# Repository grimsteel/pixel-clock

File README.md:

# The Pixel Clock

A clock-shaped PCB with 8 Neopixels and a buzzer. Built on a `CH552` MCU. Powered by two rechargeable LIR2032s.

Although this cannot actually be used as a clock, it can be used to play songs, with the neopixels flashing in sync.

Firmware using [ch554_sdcc](https://github.com/Blinkinlabs/ch554_sdcc) is in the firmware directory.

[gerber.zip](https://gerber.zip/2d/?boardUrl=%20https%3A%2F%2Fraw.githubusercontent.com%2Fgrimsteel%2Fpixel-clock%2Frefs%2Fheads%2Fmain%2Fproduction%2Fhacky-holidays.zip)

---

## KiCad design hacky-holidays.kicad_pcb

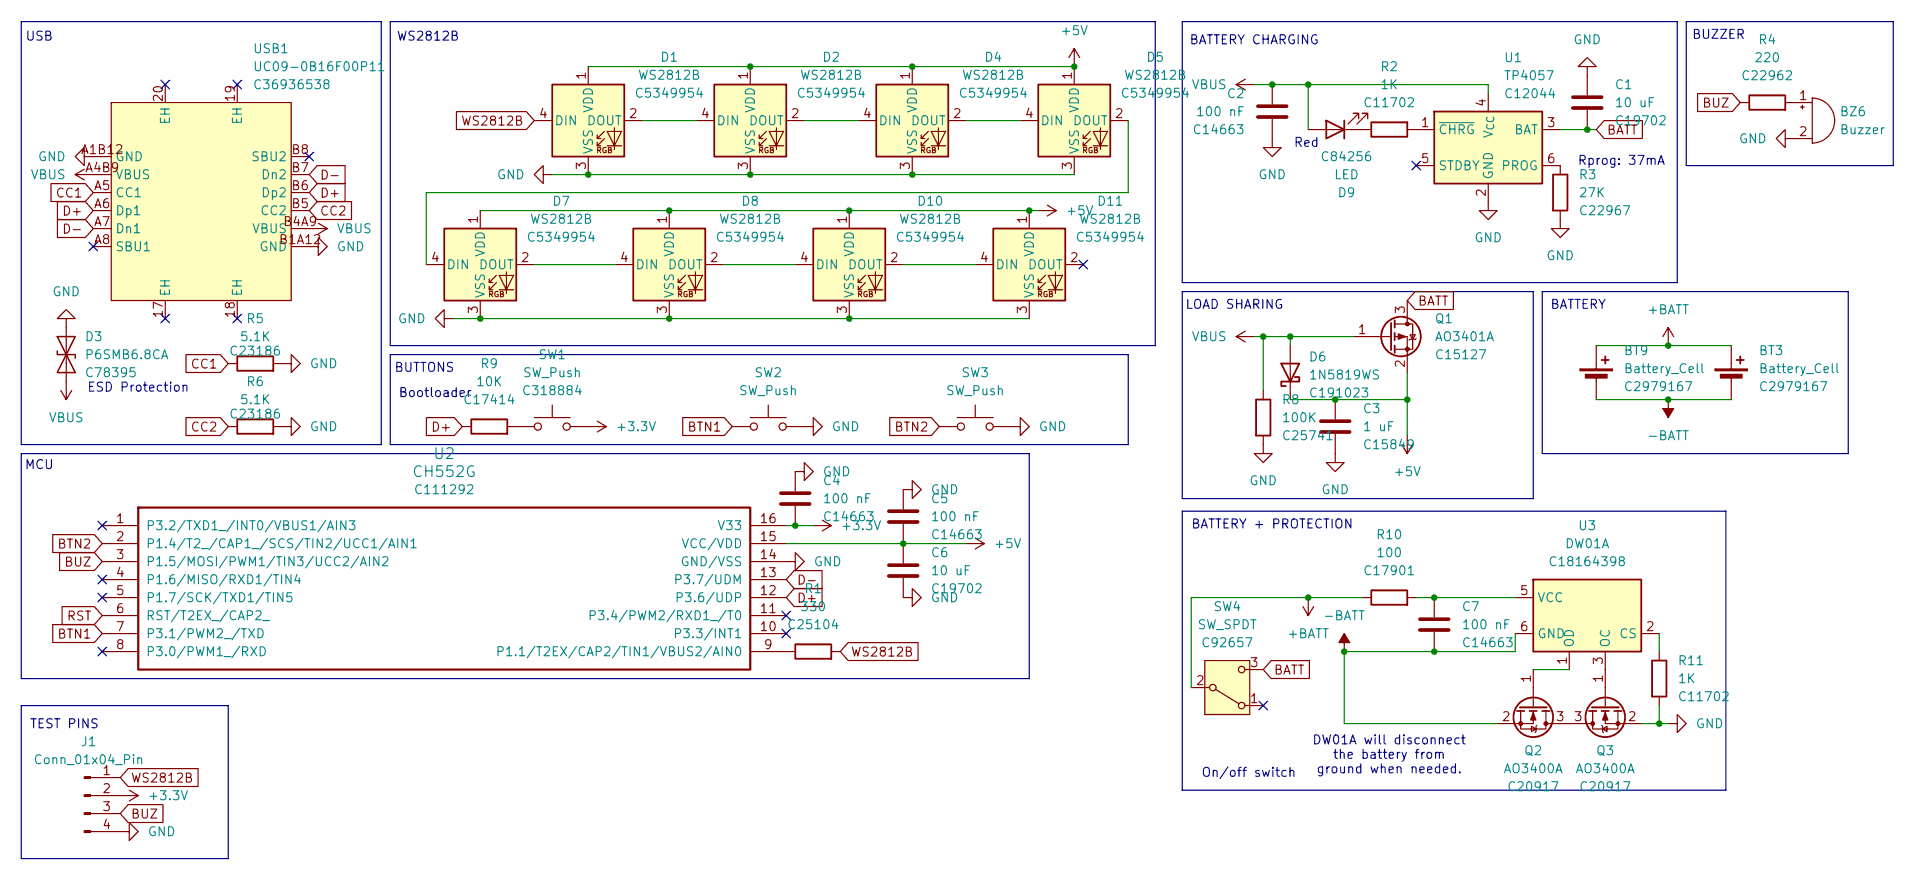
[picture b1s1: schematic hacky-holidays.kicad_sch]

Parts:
BT3, BT9: Battery_Cell; BatteryHolder_MYOUNG_BS-07-A1BJ001_CR2032; LCSC C2979167
BZ6: Buzzer; Buzzer_12x9.5RM7.6
C1, C6: 10 uF; C_0603_1608Metric; LCSC C19702
C2, C4, C5, C7: 100 nF; C_0603_1608Metric; LCSC C14663
C3: 1 uF; C_0603_1608Metric; LCSC C15849
D1, D2, D4, D5, D7, D8, D10, D11: WS2812B; LED-SMD_4P-L1.6-W1.5_XL-1615RGBC-WS2812B; LCSC C5349954
D3: P6SMB6.8CA; D_SMB; LCSC C78395
D6: 1N5819WS; D_SOD-323; LCSC C191023
D9: LED; LED_0805_2012Metric; LCSC C84256
J1: Conn_01x04_Pin; PinHeader_1x04_P2.54mm_Vertical
Q1: AO3401A; SOT-23; LCSC C15127
Q2, Q3: AO3400A; SOT-23; LCSC C20917
R1: 330; R_0402_1005Metric; LCSC C25104
R2, R11: 1K; R_0402_1005Metric; LCSC C11702
R3: 27K; R_0603_1608Metric; LCSC C22967
R4: 220; R_0603_1608Metric; LCSC C22962
R5, R6: 5.1K; R_0603_1608Metric; LCSC C23186
R8: 100K; R_0402_1005Metric; LCSC C25741
R9: 10K; R_0805_2012Metric; LCSC C17414
R10: 100; R_1206_3216Metric; LCSC C17901
SW1: SW_Push; SW_Push_1P1T_XKB_TS-1187A; LCSC C318884
SW2, SW3: SW_Push; SW_PUSH-12mm
SW4: SW_SPDT; SW-TH_K3-1260D-L1; LCSC C92657
U1: TP4057; SOT-23-6; LCSC C12044
U2: CH552G; STC_SOP-16_3.9x9.9mm_P1.27mm; LCSC C111292
U3: DW01A; SOT-23-6; LCSC C18164398
USB1: UC09-0B16F00P11; USB-C_UC09-0B16F00P11; LCSC Part C36936538

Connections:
+3.3V: C4.2, J1.2, SW1.2, U2.16 (V33)
+5V: C3.1, C5.1, C6.2, D1.1 (VDD), D2.1 (VDD), D4.1 (VDD), D5.1 (VDD), D6.1 (K), D7.1 (VDD), D8.1 (VDD), D10.1 (VDD), D11.1 (VDD), Q1.2 (S), U2.15 (VCC/VDD)
+BATT: BT3.1 (+), BT9.1 (+), R10.1, SW4.2 (B)
-BATT: BT3.2 (-), BT9.2 (-), C7.2, Q2.2 (S), U3.6 (GND)
BATT: C1.2, Q1.3 (D), SW4.3 (C), U1.3 (BAT)
BTN1: SW2.1, U2.7 (P3.1/PWM2_/TXD)
BTN2: SW3.1, U2.2 (P1.4/T2_/CAP1_/SCS/TIN2/UCC1/AIN1)
BUZ: J1.3, R4.1, U2.3 (P1.5/MOSI/PWM1/TIN3/UCC2/AIN2)
CC1: R5.1, USB1.A5 (CC1)
CC2: R6.1, USB1.B5 (CC2)
D+: R9.1, U2.12 (P3.6/UDP), USB1.A6 (Dp1), USB1.B6 (Dp2)
D-: U2.13 (P3.7/UDM), USB1.A7 (Dn1), USB1.B7 (Dn2)
GND: BZ6.2 (-), C1.1, C2.2, C3.2, C4.1, C5.2, C6.1, D1.3 (VSS), D2.3 (VSS), D3.2 (A2), D4.3 (VSS), D5.3 (VSS), D7.3 (VSS), D8.3 (VSS), D10.3 (VSS), D11.3 (VSS), J1.4, Q3.2 (S), R3.2, R5.2, R6.2, R8.2, R11.2, SW2.2, SW3.2, U1.2 (GND), U2.14 (GND/VSS), USB1.A1B12 (GND), USB1.B1A12 (GND)
unnamed: BZ6.1 (+), R4.2
unnamed: D1.2 (DOUT), D2.4 (DIN)
unnamed: D2.2 (DOUT), D4.4 (DIN)
unnamed: D4.2 (DOUT), D5.4 (DIN)
unnamed: D5.2 (DOUT), D7.4 (DIN)
unnamed: D7.2 (DOUT), D8.4 (DIN)
unnamed: D9.1 (K), R2.1
unnamed: D8.2 (DOUT), D10.4 (DIN)
unnamed: D10.2 (DOUT), D11.4 (DIN)
unnamed: Q2.3 (D), Q3.3 (D)
unnamed: Q2.1 (G), U3.1 (OD)
unnamed: Q3.1 (G), U3.3 (OC)
unnamed: R9.2, SW1.1
unnamed: R3.1, U1.6 (PROG)
unnamed: R2.2, U1.1 (~CHRG)
unnamed: R1.1, U2.9 (P1.1/T2EX/CAP2/TIN1/VBUS2/AIN0)
unnamed: R11.1, U3.2 (CS)
unnamed: C7.1, R10.2, U3.5 (VCC)
RST: U2.6 (RST/T2EX_/CAP2_)
VBUS: C2.1, D3.1 (A1), D6.2 (A), D9.2 (A), Q1.1 (G), R8.1, U1.4 (V_{CC}), USB1.A4B9 (VBUS), USB1.B4A9 (VBUS)
WS2812B: D1.4 (DIN), J1.1, R1.2

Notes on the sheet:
Bootloader
On/off switch
MCU
BATTERY
DW01A will disconnect the battery from ground when needed.
Rprog: 37mA
BUZZER
Red
USB
BUTTONS
BATTERY CHARGING
BATTERY + PROTECTION
TEST PINS
LOAD SHARING
WS2812B
ESD Protection

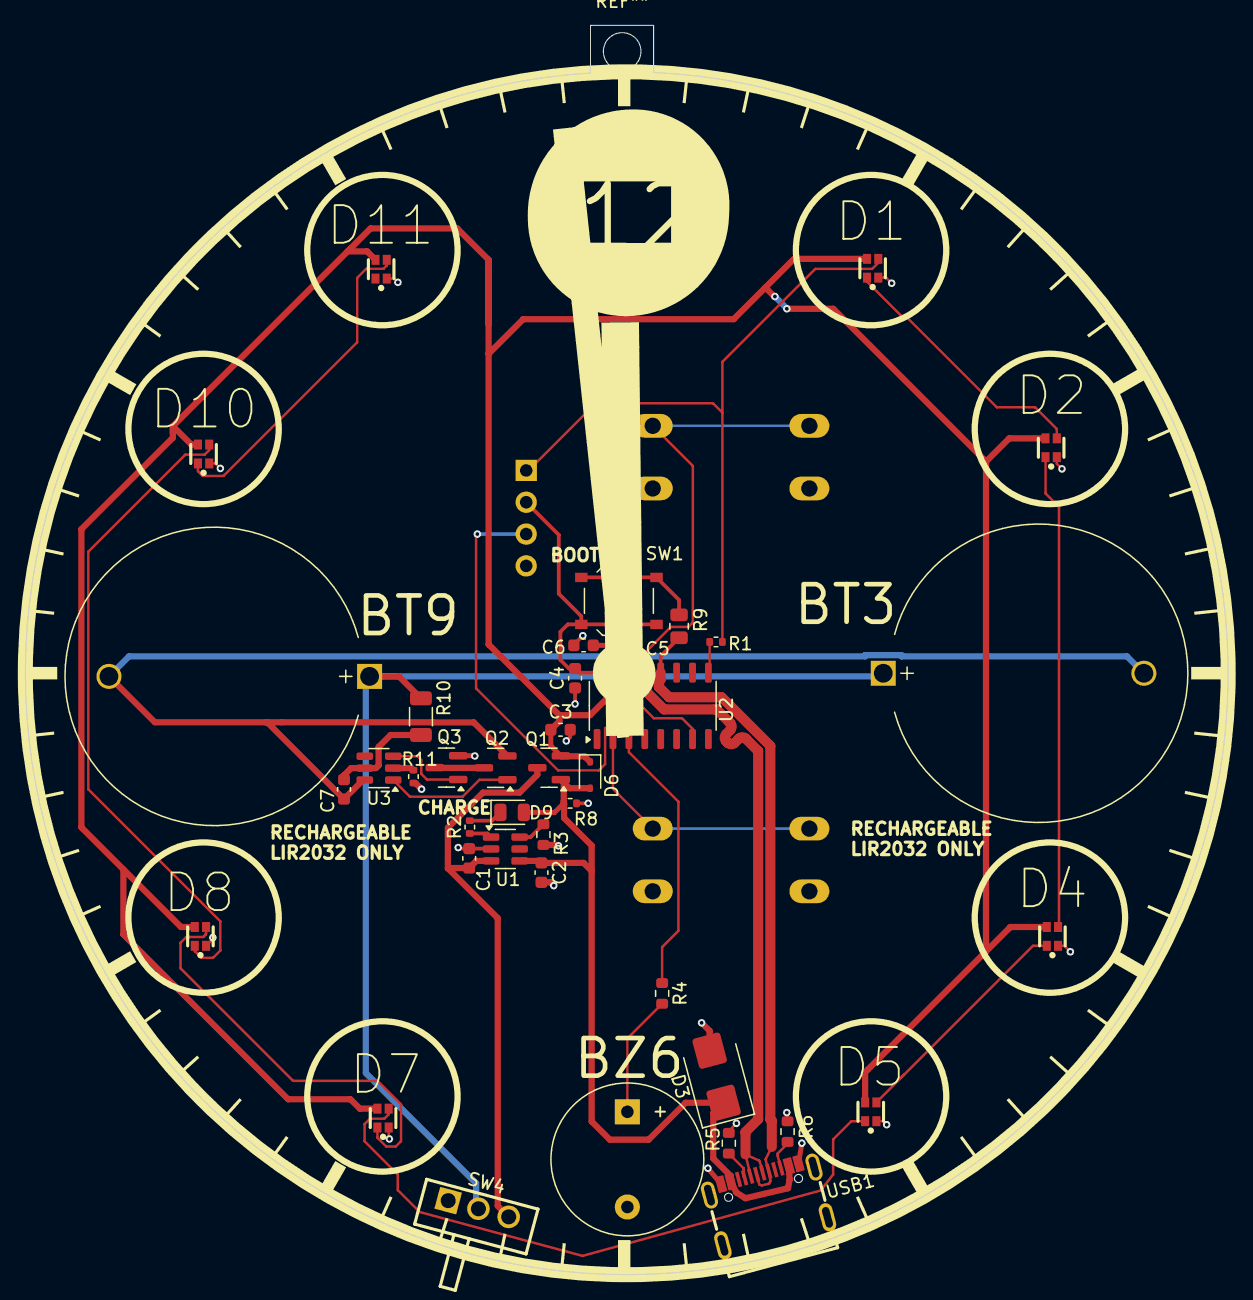
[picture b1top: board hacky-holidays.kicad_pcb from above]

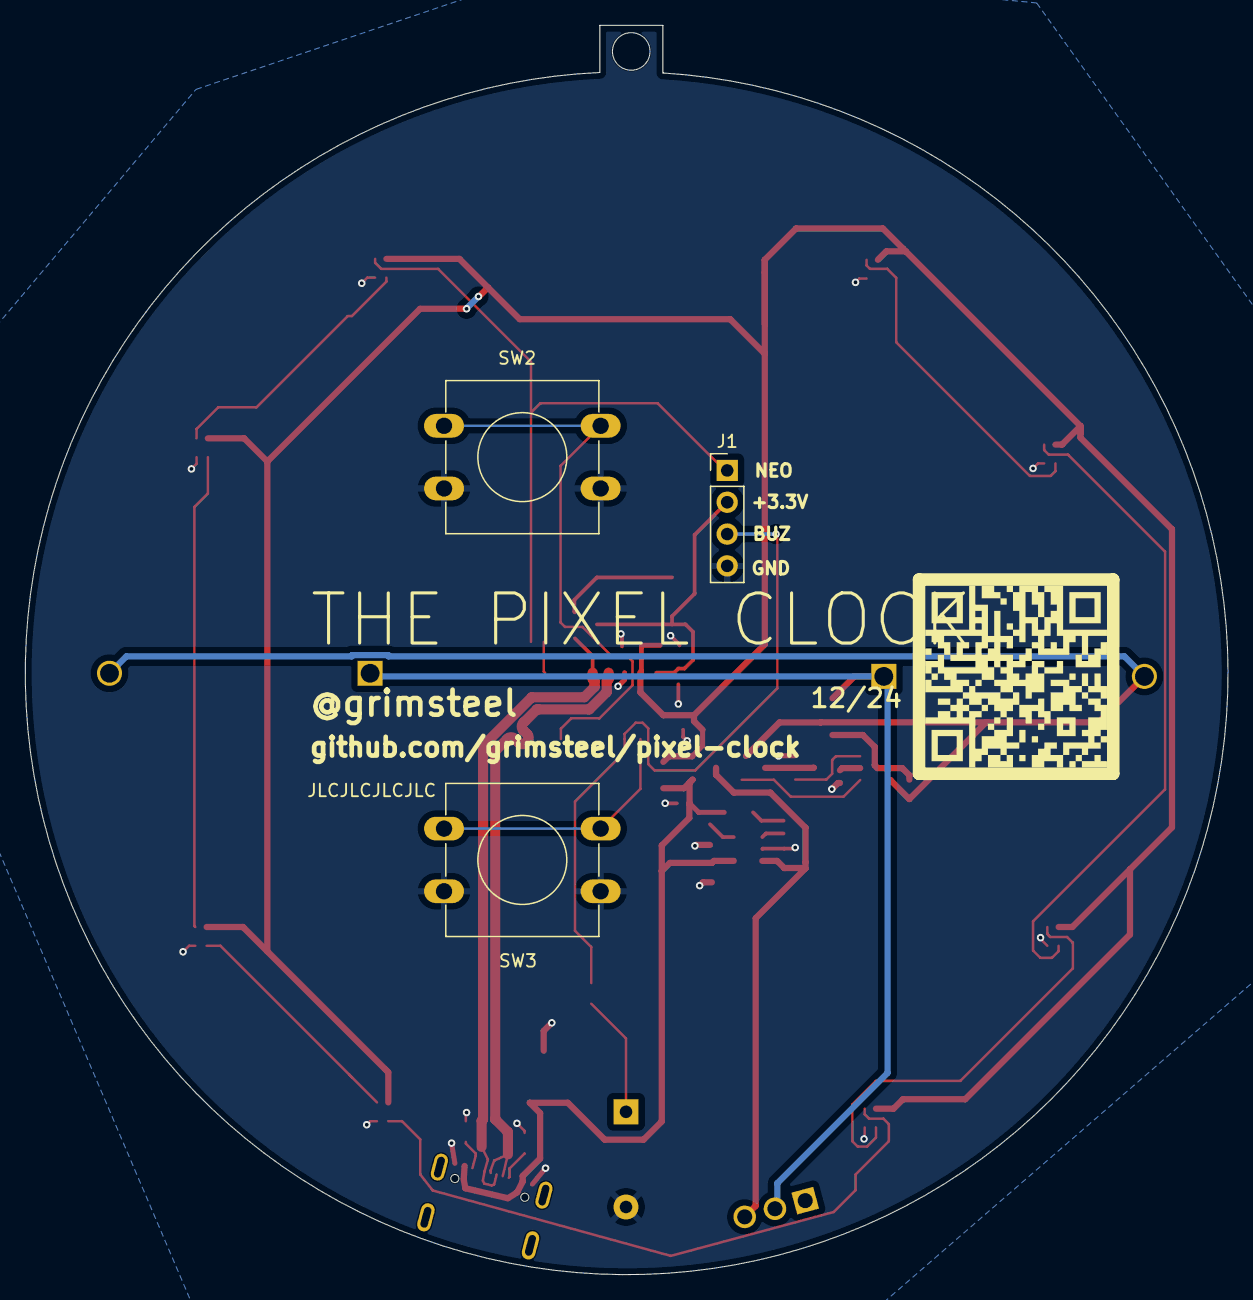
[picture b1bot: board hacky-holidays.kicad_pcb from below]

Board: 2 copper layers, 96.0 x 99.7 mm, 44 parts (4 on the bottom side), 33 nets.

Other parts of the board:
QR*****: https://github.com/grimsteel/pixel-clock; qrcode

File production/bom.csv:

Designator,Footprint,Quantity,Value,LCSC Part #
"BT3, BT9",BatteryHolder_MYOUNG_BS-07-A1BJ001_CR2032,2,Battery_Cell,C2979167
"C1, C6",0603,2,10 uF,C19702
"C2, C4, C5, C7",0603,4,100 nF,C14663
C3,0603,1,1 uF,C15849
"D1, D10, D11, D2, D4, D5, D7, D8",LED_WS2812B_PLCC4_5.0x5.0mm_P3.2mm,8,WS2812B,C22461793
D3,D_SMB,1,P6SMB6.8CA,C78395
D6,D_SOD-323,1,1N5819WS,C191023
D9,0805,1,LED,C84256
Q1,SOT-23,1,AO3401A,C15127
"Q2, Q3",SOT-23,2,AO3400A,C20917
R1,0402,1,330,C25104
R10,1206,1,100,C17901
"R11, R2",0402,2,1K,C11702
R3,0603,1,27K,C22967
R4,0603,1,220,C22962
R8,0402,1,100K,C25741
R9,0805,1,10K,C17414
SW1,SW_Push_1P1T_XKB_TS-1187A,1,SW_Push,C318884
U1,SOT-23-6,1,TP4057,C12044
U2,STC_SOP-16_3.9x9.9mm_P1.27mm,1,CH552G,C111292
U3,SOT-23-6,1,DW01A,C18164398
USB1,USB-C_UC09-0B16F00P11,1,UC09-0B16F00P11,C36936538

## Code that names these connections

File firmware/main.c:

#include "ch554.h"
#include "debug.h"
#include "programs.h"
#include "stdbool.h"

#define P1 0x90
#define P3 0xB0

// setup buttons

// BTN1: P3.1
// BTN2: P1.4
#define BTN1_PIN 1
#define BTN2_PIN 4
SBIT(BTN1, 0xB0, BTN1_PIN);
SBIT(BTN2, 0x90, BTN2_PIN);

// BUZ: P1.5
#define BUZ_PIN 5
SBIT(BUZ, 0x90, BUZ_PIN);

// WS2812B: P1.1
#define WS2812B_PIN 1
#define NUM_WS2812B 8
SBIT(WS2812B, 0x90, WS2812B_PIN);

// [0, 256)
#define WS2812B_BRIGHTNESS 5

// GRB, in order
__xdata uint8_t ws2812b_data[24];

// Timer frequency in hertz (6 MHz / 12)
#define TIMER_FREQUENCY 500000
#define HALF_TIMER_FREQUENCY 250000

uint16_t timer_ticks_start;
uint32_t toggle_count;
// this serves as the current time.
// 1 "unit" of timer1_overflows is 0.5ms
volatile uint32_t timer1_overflows = 0;
uint32_t last_button1_press = 0;
uint32_t last_button2_press = 0;
volatile uint8_t current_idx = 0;

void next_program_item();

// PWM timer interrupt
void timer0_interrupt(void) __interrupt(INT_NO_TMR0) {
  // one-half cycle has elapsed
  TL0 = timer_ticks_start & 0xff;
  TH0 = timer_ticks_start >> 8;

  if (toggle_count-- > 0) {
    // toggle pin
    BUZ = !BUZ;
  } else {
    // turn off
    BUZ = 0;
    // stop the timer, disable interrupt
    TMOD &= ~bT0_M0;
    TR0 = 0;

    // wait 100ms before next item
    mDelaymS(100);
    next_program_item();
  }
}

// Main timer interrupt
void timer1_interrupt(void) __interrupt(INT_NO_TMR1) { timer1_overflows++; }

inline void btn1_press() {
  SAFE_MOD = 0x55;
  SAFE_MOD = 0xAA;

  // Reset
  GLOBAL_CFG |= bSW_RESET;

  // exit safe mode
  SAFE_MOD = 0x00;
}
inline void btn2_press() {}

// GPIO interurpt
void gpio_interrupt(void) __interrupt(INT_NO_GPIO) {
  if (!BTN1) {
    // if last_button1_press < timer1_overflows, the program has been running for 25 days, and we overflowed the unsigned int
    if (last_button1_press < timer1_overflows && timer1_overflows - last_button1_press >= 20) {
      btn1_press();
    }
    last_button1_press = timer1_overflows;
  }

  if (!BTN2) {
    if (last_button2_press < timer1_overflows && timer1_overflows - last_button2_press >= 20) {
      btn2_press();
    }
    last_button2_press = timer1_overflows;
  }
}

// PWM - 50% duty cycle
// Builtin PWM is too fast for audible tones
// Duration is measured in 16th notes (250ms)
void tone(uint16_t frequency_hz, uint8_t duration) {
  // already playing a tone
  if (TR0 == 1) return;
  
  // TODO: Higher frequencies may be able to use a faster clock (bT0_CLK, bTMR_CLK)

  ET0 = 1; // timer0 interrupt
  TMOD |= bT0_M0; // 16 bit timer0

  // Adapted from arduino tone() code
  // TIMER_FREQUENCY / frequency_hz returns number of ticks for a full cycle
  // Because this is 50% duty cycle, divide by 2 for number of ticks for each "high" or each "low"
  // We will start counting at this value, and go to 0xffff
  // idk what the +1 is for
  timer_ticks_start = 0xffff - (uint16_t) ((uint32_t) (HALF_TIMER_FREQUENCY) / frequency_hz) + 1;
  // frequency * duration = number of full cycles
  // * 2 = number of toggles
  // / 1000 because ms
  // toggle_count = (uint32_t) (frequency_hz * duration_ms) / 1000 * 2;
  // optimized version: measure duration as 1/4 second
  toggle_count = frequency_hz * duration >> 1;

  // Set the timer
  TL0 = timer_ticks_start & 0xff;
  TH0 = timer_ticks_start >> 8;

  TR0 = 1; // begin timer
}

__data uint8_t byte_count = 24;
__data uint8_t bit_count;

void ws2812b_write() {
  // disable interrupts (time sensitive!)
  E_DIS = 1;
  //for (uint8_t i = 0; i < NUM_WS2812B * 3; i++) {
    // TIMINGS AT 6MHz (tolerance 150 ns aka 1 clock cycle)
    // T1H = 0.9 us --> 6 clock cycles
    // T1L = 0.3 us --> 2 clock cycles
    // T0H = 0.3 us -> 2 clock cycles
    // T0L = 0.9 us --> 6 clock cycles
    // The low times don't _really_ matter - only the high times matter for distinguishing between 0s and 1s
    // RESET TIME: > 50 us --> 300 clock cycles
    // Total time: 7/8 clock cycles
    // TODO: Tune with a logic analyzer
    __asm
    mov dptr, #_ws2812b_data
02$:
    movx A, @dptr
    mov _bit_count, #8 ; eight bits
01$:            ; --- loop
    rlc A           ; 1 cycle
    setb _WS2812B   ; 1 cycle - T1H begin + T0H begin + T0L end (2 + 1 + 2 + 1) + T1L end (1 + 2 + 1)
    mov _WS2812B, C ; 2 cycles - T0H end (1 + 1) + T0L begin
    nop             ; 1 cycle
    clr _WS2812B    ; 1 cycle - T1H end (1 + 1 + 2) + T1L begin
    djnz _bit_count, 01$    ; 2 cycles
    inc dptr
    djnz _byte_count, 02$
    __endasm;
    //  }
  // re-enable interrupts
  E_DIS = 0;
}

// Hues is an array of length NUM_WS2812B
void ws2812b_set_hues(uint16_t *hues) {
  for (int i = 0; i < NUM_WS2812B; i++) {
    uint16_t hue = hues[i];
    uint8_t r = 0, g = 0, b = 0;
    uint8_t sector = hue / 60;
    switch (sector) {
    case 5: // [300, 360)
      r = WS2812B_BRIGHTNESS;
      b = WS2812B_BRIGHTNESS * 6 - WS2812B_BRIGHTNESS * hue / 60;
      break;
    case 0: // [0, 60)
      r = WS2812B_BRIGHTNESS;
      g = WS2812B_BRIGHTNESS * hue / 60;
      break;
      
    case 1: // [60, 120)
      g = WS2812B_BRIGHTNESS;
      r = WS2812B_BRIGHTNESS * 2 - WS2812B_BRIGHTNESS * hue / 60;
      break;
    case 2:
      g = WS2812B_BRIGHTNESS;
      b = WS2812B_BRIGHTNESS * hue / 60 - WS2812B_BRIGHTNESS * 2;
      break;
      
    case 3:
      b = WS2812B_BRIGHTNESS;
      g = WS2812B_BRIGHTNESS * 4 - WS2812B_BRIGHTNESS * hue / 60;
      break;
    case 4:
      b = WS2812B_BRIGHTNESS;
      r = WS2812B_BRIGHTNESS * hue / 60 - WS2812B_BRIGHTNESS * 4;
      break;
    }
    ws2812b_data[i * 3] = g / 20;
    ws2812b_data[i * 3 + 1] = r / 20;
    ws2812b_data[i * 3 + 2] = b / 20;
  }
}

void set_ws2812b(int i, uint8_t* colors, bool clear) {
  ws2812b_data[i * 3] = !clear ? colors[0] : 0;
  ws2812b_data[i * 3 + 1] = !clear ? colors[1] : 0;
  ws2812b_data[i * 3 + 2] = !clear ? colors[2] : 0;
}

void next_program_item() {
  if (current_idx == PROGRAM1_LENGTH)  {
    // wait 1 second before repeating
    current_idx = 0;
  }
  for (int j = 0; j < 24; j++) ws2812b_data[j] = 0;
  //uint16_t hues[NUM_WS2812B];
  for (int j = 0; j < NUM_WS2812B; j++) {
    if (j == (current_idx / 2)) set_ws2812b(j, program1_colors[current_idx], false);
    else if (j - 4 == (current_idx / 2)) set_ws2812b(j, program1_colors[current_idx + 1], false);
    //else set_ws2812b(j, 0, true);
  }
  //ws2812b_set_hues(hues);
  ws2812b_write();
  
  // buzzer
  //tone(program_1_notes[current_idx], program_1_durations[current_idx]);
  current_idx+=2;
}

void main() {
  // frequency is default (6MHz)
  CfgFsys(); // no need for this
  mDelaymS(5);

  /*// enter safe mode
  SAFE_MOD = 0x55;
  SAFE_MOD = 0xAA;
  
  // setup sleep wake on buttons
  WAKE_CTRL |= bWAK_P1_4_LO | bWAK_P3_2E_3L; // 3.2 is disconnected

  // exit safe mode
  SAFE_MOD = 0x00;*/

  mInitSTDIO();
  UART1Setup();

  // disable all pullups except for 1.2 and 1.3 (clock)
  P1_DIR_PU &= 0x0C;
  // disable all except for 3.6 and 3.7 (usb)
  P3_DIR_PU &= 0xC0;
  
  // push pull mode
  P1_MOD_OC &= ~(1 << WS2812B_PIN);
  // output mode
  P1_DIR_PU |= 1 << WS2812B_PIN;

  WS2812B = 0;
  

  P1_MOD_OC &= ~(1 << BUZ_PIN);
  P1_DIR_PU |= 1 << BUZ_PIN;
  BUZ = 0;

  // configure buttons as high impedance with pullup
  P1_MOD_OC |= 1 << BTN2_PIN;
  P1_DIR_PU |= 1 << BTN2_PIN;

  P3_MOD_OC |= 1 << BTN1_PIN;
  P3_DIR_PU |= 1 << BTN1_PIN;

  // enable interrupts
  EA = 1;
  // gpio interrupts
  IE_GPIO = 1;
  // gpio edge interrupt mode, enable on 1.4 and 3.1
  GPIO_IE |= bIE_IO_EDGE | bIE_P1_4_LO | bIE_P3_1_LO;

  TMOD |= bT1_M1;// 8 bit timer1 (0.5 ms for each overflow - 256 / (6 MHz / 12) = 512 us)
  TR1 = 1;

  // start program
  while (true) {
      next_program_item();
      mDelaymS(1000);
  }
  
}

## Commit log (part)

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2024-12-28 add license
2024-12-28 add remaining neopixel lcsc ids
2024-12-28 add clock outline
2024-12-28 add usb lcsc part
2024-12-28 add production files
2024-12-31 add firmware
2024-12-31 update capacitor part numbers, add test pins, silkscreen updates
2024-12-31 tidy schematic
2024-12-31 add mounting hole
2025-01-01 add images
2025-01-01 add schematic image
2025-01-01 make pcb below 100x100
2025-01-01 use absolute links for images
2025-01-02 invert qr code
2025-01-02 add usb cc resistors
2025-01-24 use economic ws2812bs
2025-01-25 fix designators
